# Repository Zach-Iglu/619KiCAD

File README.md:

# 619KiCAD
Cavalier Robotics KiCAD Codebase for the 2022 Robot

## Quick Links
[Clavier Robotics 619](https://github.com/619Code)

[Wiring Diagram](https://app.diagrams.net/#G1v4SkuMv3gRLgb3_6xDDtmYxPFZdRlgS9)

## Software Required
[KiCAD](https://www.kicad.org/)

[Github Desktop](https://desktop.github.com/)

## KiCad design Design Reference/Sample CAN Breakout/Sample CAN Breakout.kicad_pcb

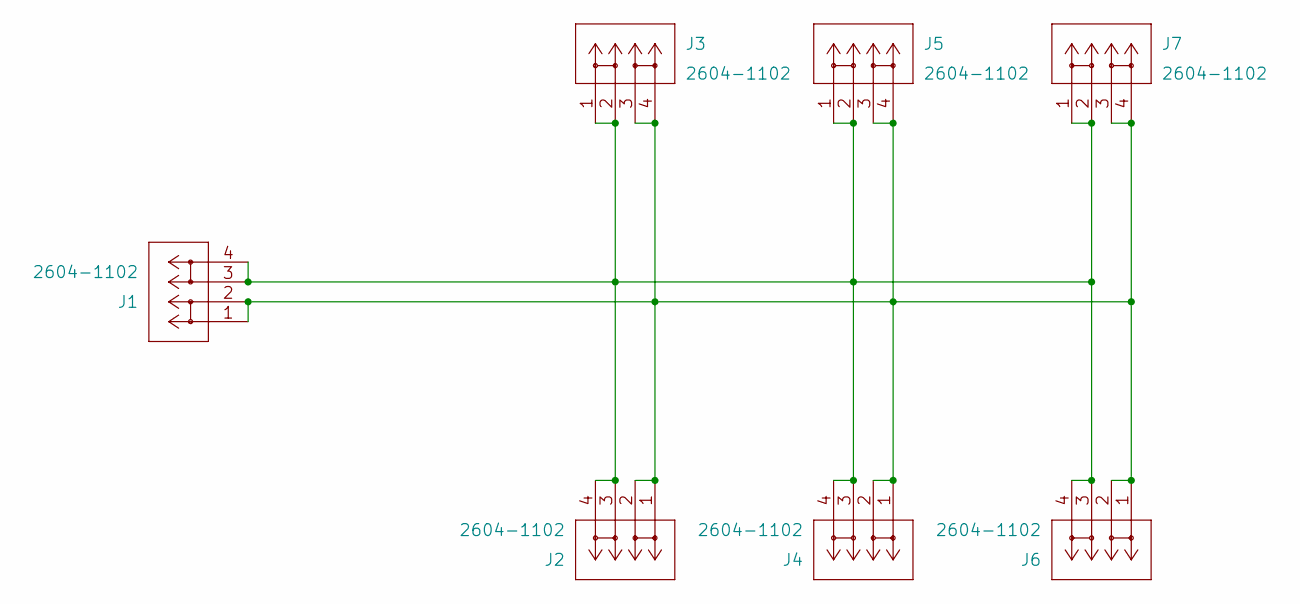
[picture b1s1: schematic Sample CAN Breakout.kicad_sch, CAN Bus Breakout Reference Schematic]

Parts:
J1, J2, J3, J4, J5, J6, J7: 2604-1102; Wago_Terminal_Block_2

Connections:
unnamed: J1.1, J1.2, J2.1, J2.2, J3.3, J3.4, J4.1, J4.2, J5.3, J5.4, J6.1, J6.2, J7.3, J7.4
unnamed: J1.3, J1.4, J2.3, J2.4, J3.1, J3.2, J4.3, J4.4, J5.1, J5.2, J6.3, J6.4, J7.1, J7.2

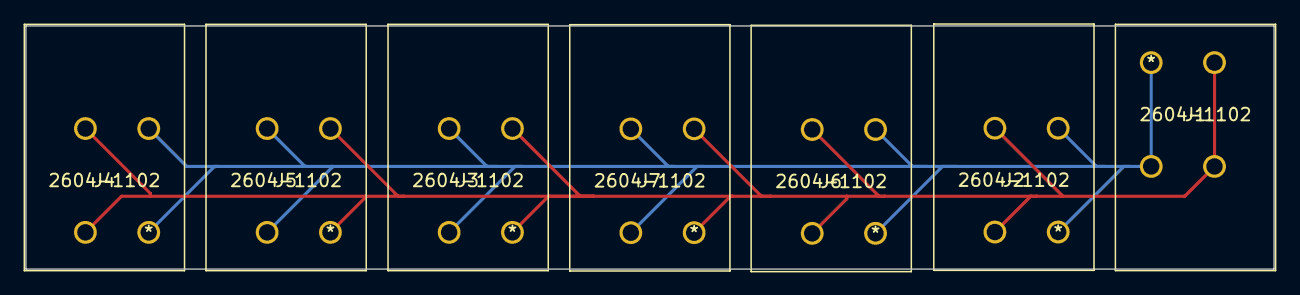
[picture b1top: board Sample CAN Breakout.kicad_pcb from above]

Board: 2 copper layers, 98.6 x 19.2 mm, 7 parts (0 on the bottom side), 2 nets.

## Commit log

2022-09-29 Update README.md
    Updated to Draw.io
2022-10-08 Limelight and RoboRio
2022-10-08 First_Robotics.kaicad_sym upload
    Has Neo, Neo 550, PCM, PDP, Spark_Max, VRM
2022-10-08 Files into folder
2022-10-08 Update quick links
2022-10-14 Began circuit diagram on PDP and Motor Controllers
2022-11-11 Moved some things around
    Not really any change but moved to make more readable
2023-01-12 Upload of Wago 2 Pin Terminal Block Part
2023-01-12 Part Aggregtion
    - Gathered WAGO Part
    - Began KiCAD CAN Bus Breakout Design Reference Script
    - Fully Imported the Wago model
    - Layed out sample design
    - Annotated and rats nest laid out
2023-01-12 Reference Design 1 Finished
    Ruler Reference Design Finished

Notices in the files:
parts and their libraries:
Copyright 2021 Accelerated Designs. All rights reserved.
